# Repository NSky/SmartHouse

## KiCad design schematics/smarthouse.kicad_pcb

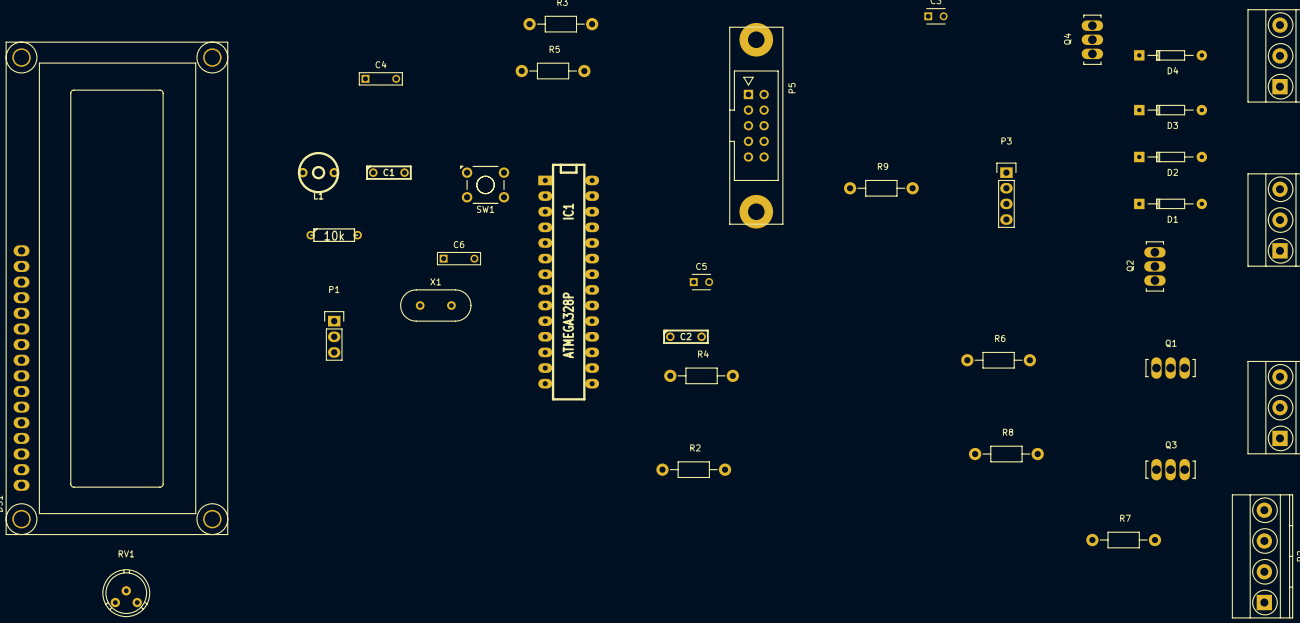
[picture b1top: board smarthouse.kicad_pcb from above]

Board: 2 copper layers, 36 parts (0 on the bottom side), 37 nets, no tracks yet.

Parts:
C1: 47uF; C2
C2: 100n; C2
C3, C5: 12...22pF; C_Disc_D3_P2.5
C4, C6: 100n; C_Rect_L7_W2_P5
D1, D2, D3, D4: D; Diode_DO-35_SOD27_Horizontal_RM10
DS1: LCD-016N002L; WC1602A
IC1: ATMEGA328P; DIP-28__300_ELL
L1: 120uH; CV3-30PF
P1: UART; Pin_Header_Straight_1x03
P2: COUNTERS; TerminalBlock_Pheonix_MKDS1.5-4pol
P3: CONN_01X04; Pin_Header_Straight_1x04
P4: TEMP SENSOR; TerminalBlock_Pheonix_MKDS1.5-3pol
P5: CONN_02X05; he10-10d
P6, P7: CONN_01X03; TerminalBlock_Pheonix_MKDS1.5-3pol
Q1, Q2, Q3, Q4: MJE13003 КТ815; SOT126_SOT32_Housing_Vertical_BigPads
R1: 10k; R3
R2, R3, R4, R5: 10k; Resistor_Horizontal_RM10mm
R6, R7, R8, R9: 270R; Resistor_Horizontal_RM10mm
RV1: 10k; Potentiometer_Bourns_3339H_Angular_ScrewUp
SW1: RESET; SW_TH_Tactile_Omron_B3F-10xx
X1: 8MHz; HC-49V

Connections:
+3V3: C1.1, C2.1, DS1.2, DS1.15, IC1.7, L1.1, P4.1, P5.2, R1.2, R2.1, R3.1, R4.1, R5.1, RV1.1
+12V: D1.1, D2.1, D3.1, D4.1, P6.2, P7.2
GND: C1.2, C2.2, C3.2, C4.2, C5.2, C6.2, DS1.1, DS1.5, DS1.16, IC1.8, IC1.22, P1.3, P2.2, P2.4, P3.2, P3.4, P4.3, P5.4, P5.6, P5.8, P5.10, Q1.1, Q2.1, Q3.1, Q4.1, RV1.3, SW1.1
unnamed: C3.1, IC1.9, X1.2
unnamed: C4.1, IC1.20, L1.2
unnamed: C5.1, IC1.10, X1.1
unnamed: C6.1, IC1.21
unnamed: D1.2, P6.1, Q1.2
unnamed: D2.2, P7.1, Q2.2
unnamed: D3.2, P6.3, Q3.2
unnamed: D4.2, P7.3, Q4.2
unnamed: DS1.3, RV1.2
unnamed: DS1.4, IC1.4
unnamed: DS1.6, IC1.5
unnamed: DS1.11, IC1.6
unnamed: DS1.12, IC1.11
unnamed: DS1.13, IC1.12
unnamed: DS1.14, IC1.13
unnamed: IC1.2, P1.1
unnamed: IC1.3, P1.2
unnamed: IC1.14, P2.1, R2.2
unnamed: IC1.15, P2.3, R3.2
unnamed: IC1.16, P4.2
unnamed: IC1.17, P5.1
unnamed: IC1.18, P5.9
unnamed: IC1.19, P5.7
unnamed: IC1.23, R6.1
unnamed: IC1.24, R8.1
unnamed: IC1.25, R7.1
unnamed: IC1.26, R9.1
unnamed: IC1.27, P3.1, R4.2
unnamed: IC1.28, P3.3, R5.2
unnamed: Q1.3, R6.2
unnamed: Q2.3, R7.2
unnamed: Q3.3, R8.2
unnamed: Q4.3, R9.2
RESET: IC1.1, P5.5, R1.1, SW1.2

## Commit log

2016-12-26 ERC fixed. Unneeded files deleted.
2016-12-26 -rescue library removed
2016-12-26 scheme changed
2016-12-26 power flags added
2016-12-26 components approximate dimensions written down
2016-12-26 layout drafts added
